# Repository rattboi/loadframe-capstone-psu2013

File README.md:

loadframe-capstone-psu2013
==========================

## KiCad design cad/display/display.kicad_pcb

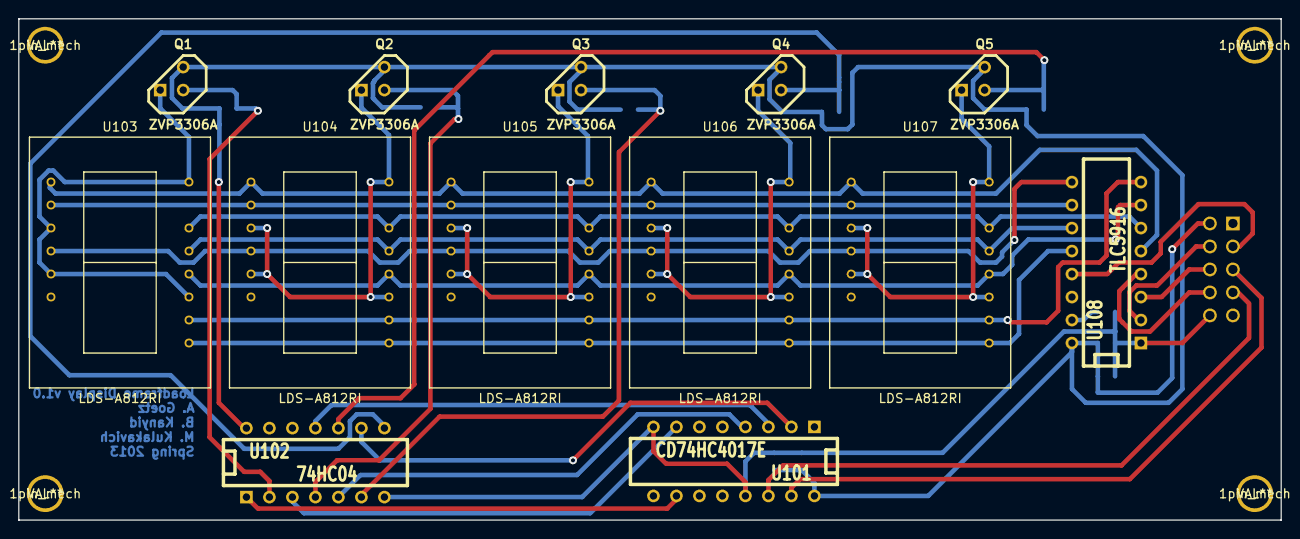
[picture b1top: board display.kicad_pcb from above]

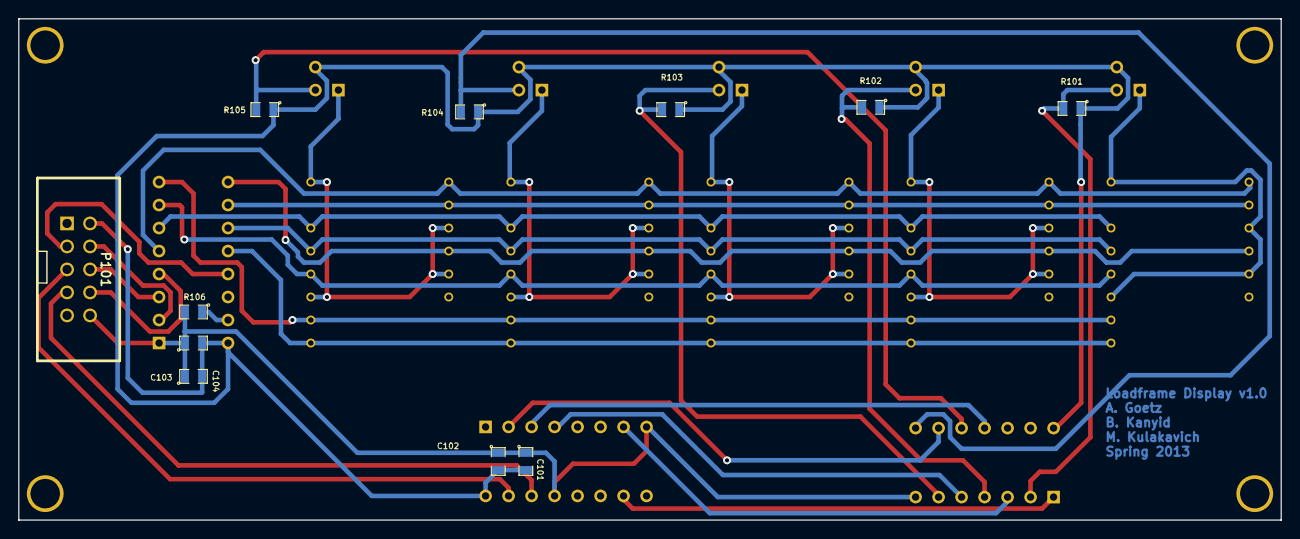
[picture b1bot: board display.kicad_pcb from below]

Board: 2 copper layers, 139.4 x 55.4 mm, 28 parts (11 on the bottom side), 32 nets.

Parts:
1pin_mech, 1pin_mech#2, 1pin_mech#3, 1pin_mech#4: VAL**; 1pin_mech
C101, C103: 100nF; SM0805
C102, C104: 1uF; SM0805
P101: CONN_5X2; shrouded_5x2
Q1, Q2, Q3, Q4, Q5: ZVP3306A; TO92-123
R101, R102, R103, R104, R105: 10K; SM0805
R106: 750; SM0805
U101: CD74HC4017E; DIP-16__300
U102: 74HC04; DIP-14__300
U103, U104, U105, U106, U107: LDS-A812RI
U108: TLC5916; DIP-16__300

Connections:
+5V: C101.2, C102.2, C103.2, C104.2, P101.2, Q1.1, Q2.1, Q3.1, Q4.1, Q5.1, R101.1, R102.1, R103.1, R104.1, R105.1, U101.16, U102.14, U108.16
/A: U103.1, U104.1, U105.1, U106.1, U107.1, U108.5
/B: U103.14, U104.14, U105.14, U106.14, U107.14, U108.6
/C: U103.12, U104.12, U105.12, U106.12, U107.12, U108.7
/D: U103.10, U104.10, U105.10, U106.10, U107.10, U108.8
/E: U103.4, U104.4, U105.4, U106.4, U107.4, U108.9
/F: U103.2, U104.2, U105.2, U106.2, U107.2, U108.10
/G: U103.13, U104.13, U105.13, U106.13, U107.13, U108.11
/RDP: U103.9, U104.9, U105.9, U106.9, U107.9, U108.12
GND: C101.1, C102.1, C103.1, C104.1, P101.10, R106.2, U101.8, U101.13, U102.7, U108.1
unnamed: Q4.3, U106.3, U106.5, U106.11, U106.16
unnamed: U101.3, U102.11
unnamed: Q1.3, U103.3, U103.5, U103.11, U103.16
unnamed: U101.10, U102.1
unnamed: R106.1, U108.15
unnamed: P101.3, U108.13
unnamed: P101.8, U108.4
unnamed: P101.6, U108.3
unnamed: P101.4, U108.2
unnamed: U101.7, U102.3
unnamed: Q5.2, R105.2, U102.10
unnamed: Q4.2, R104.2, U102.8
unnamed: Q1.2, R101.2, U102.2
unnamed: Q2.3, U104.3, U104.5, U104.11, U104.16
unnamed: Q3.2, R103.2, U102.6
unnamed: Q3.3, U105.3, U105.5, U105.11, U105.16
unnamed: U101.2, U102.9
unnamed: Q2.2, R102.2, U102.4
unnamed: Q5.3, U107.3, U107.5, U107.11, U107.16
unnamed: U101.4, U102.5
unnamed: P101.7, U101.14
unnamed: P101.5, U101.15

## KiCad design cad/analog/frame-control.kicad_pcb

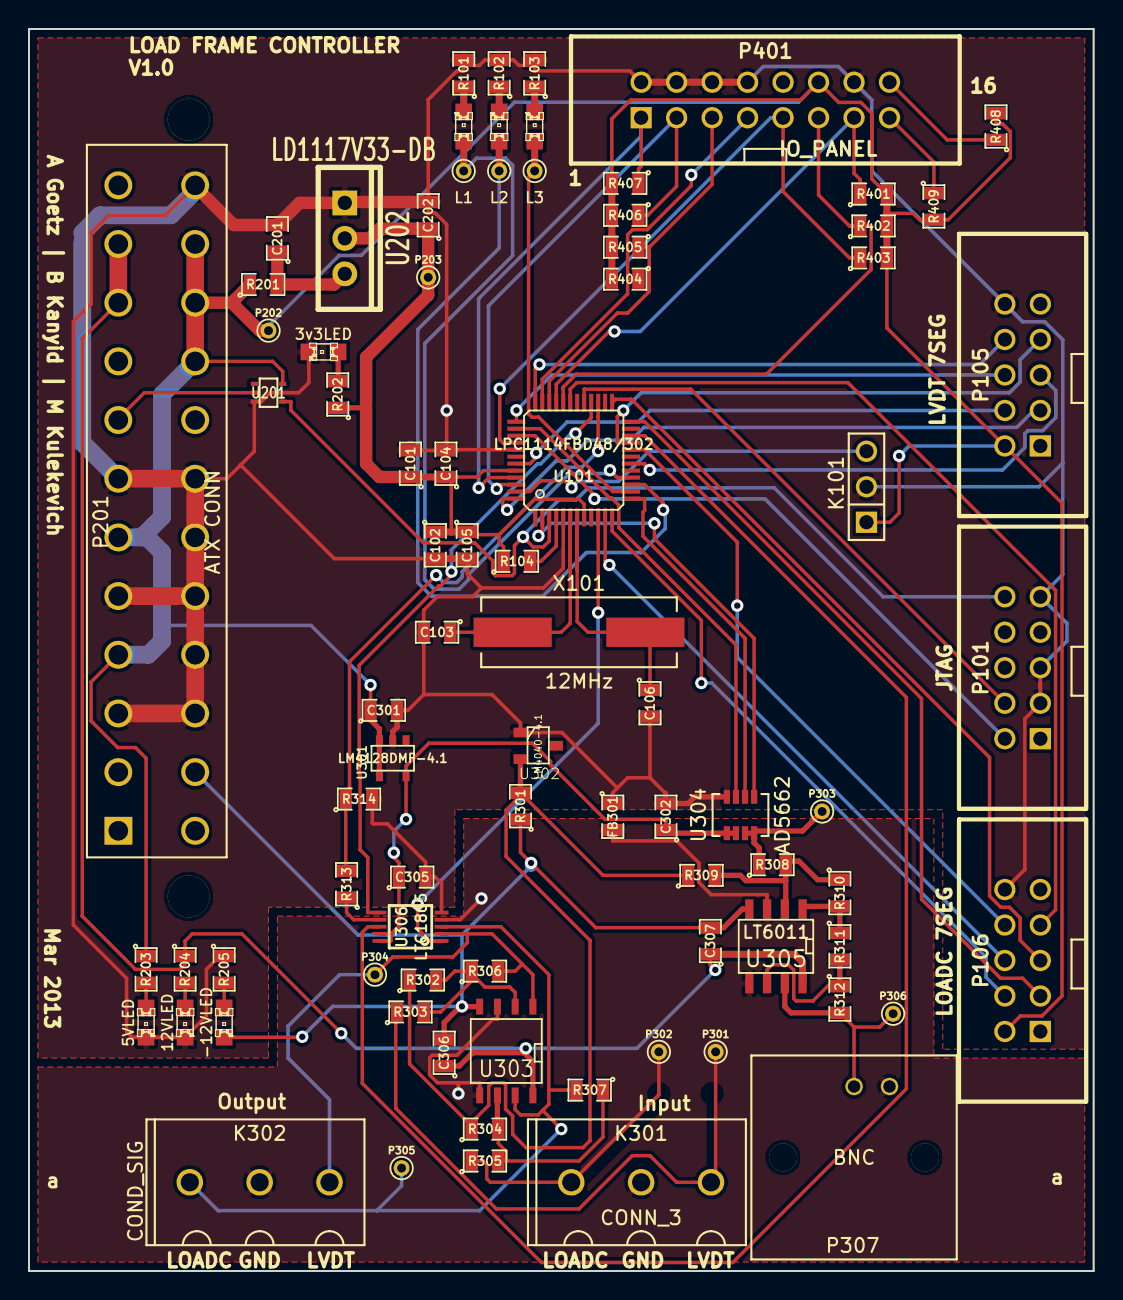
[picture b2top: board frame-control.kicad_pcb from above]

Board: 2 copper layers, 76.2 x 88.9 mm, 83 parts (0 on the bottom side), 67 nets.

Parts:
C101, C102, C302, C305, C306, C307: 100n; SM0805
C103, C106: 18pF; SM0805
C104, C105: 10n; SM0805
C201, C202: 1u; SM0805
C301: 4.7u; SM0805
D101: L1; LED-0805
D102: L2; LED-0805
D103: L3; LED-0805
D201: 3v3LED; LED-0805
D202: 5VLED; LED-0805
D203: 12VLED; LED-0805
D204: -12VLED; LED-0805
FB301: FILTER; SM0805
K101: LCD; PIN_ARRAY_3X1
K301: CONN_3; OSTTA030161
K302: COND_SIG; OSTTA030161
P101: JTAG; shrouded_5x2
P102, P103, P104, P202, P203, P301, P302, P303, P304, P305, P306: TST; PINTST
P105: LVDT; shrouded_5x2
P106: LOADC; shrouded_5x2
P201: ATX CONN; 39-29-9242
P307: BNC; TE-1-1634612-0
P401: IO_PANEL; shrouded_8x2
R101, R102, R103, R202, R203, R204, R205: 1.5k; SM0805
R104, R306, R307, R308, R310, R313, R314, R403, R404, R405, R406, R407, R408, R409: 10k; SM0805
R201: 0; SM0805
R301: 500; SM0805
R302, R304, R309: 20k; SM0805
R303, R305: 59k; SM0805
R311: 17k; SM0805
R312: 100k; SM0805
R401, R402: 5.1k; SM0805
U101: LPC1114FBD48/302; lqfp48
U201: 74LVCE1G06; SOT353
U202: LD1117V33-DB; TO220_VERT_FIX
U301: LM4128DMF-4.1; SOT23-5
U302: LM4040-4.1; SOT23
U303: LT6011; SO8N
U304: AD5662; SOT23-8
U305: LT6011; SO8E
U306: LTC1865; MSOP10-0.5
X101: 12MHz; HC-49-US

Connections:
+3.3V: C101.1, C102.1, C104.1, C105.1, C202.1, P203.1, R104.1, R202.1, U101.8, U101.44, U202.2
+5V: C301.1, K101.1, P105.2, P106.2, P201.4, P201.6, P201.21, P201.22, P201.23, P202.1, P401.12, R201.1, R203.1, R401.2, R402.2, R403.2, R404.2, R405.2, R406.2, R407.2, R408.2, R409.2, U201.5, U301.3, U301.4
+5VA: C302.1, C305.1, U301.5, U304.1, U304.2, U306.9, U306.10
+12V: C306.1, C307.1, P201.10, P201.11, R204.1, U303.8, U305.8
-12V: C306.2, C307.2, D204.2, P201.14, R301.1, U303.4, U305.4
/Analog Frontend/ADCCLK: U101.22, U306.8
/Analog Frontend/ADCEN: U101.10, U306.1
/Analog Frontend/ADCI: U101.28, U306.6
/Analog Frontend/ADCO: R313.2, R314.1, U101.27
/Analog Frontend/DACCLK: U101.13, U304.6
/Analog Frontend/DACIN: U101.38, U304.7
/Analog Frontend/~DACEN: U101.2, U304.5
/InterfaceButtons/Aux1: P401.15, R409.1
/InterfaceButtons/Aux2: P401.16, R408.1
/InterfaceButtons/ESTOP: P401.5, R405.1, U101.34
/InterfaceButtons/EncoderA: P401.11, R402.1, U101.32
/InterfaceButtons/EncoderB: P401.13, R401.1, U101.33
/InterfaceButtons/TareLOADC: P401.3, R406.1, U101.46
/InterfaceButtons/TareLVDT: P401.1, R407.1, U101.45
/InterfaceButtons/ToggleA: P401.7, R404.1, U101.35
/InterfaceButtons/ToggleB: P401.9, R403.1, U101.40
/Power/PWRGD: P101.10, U101.3, U201.4
AGND: FB301.2, K301.2, K302.2, P307.2, U303.3, U303.5, U305.3, U305.5, U306.4
GND: C101.2, C102.2, C103.2, C104.2, C105.2, C106.2, C201.2, C202.2, C301.2, C302.2, C305.2, D201.2, D202.2, D203.2, FB301.1, K101.2, P101.3, P101.5, P101.9, P105.10, P106.10, P201.3, P201.5, P201.7, P201.15, P201.16, P201.17, P201.18, P201.19, P201.24, P401.2, P401.4, P401.6, P401.8, P401.14, R101.2, R102.2, R103.2, R205.1, R314.2, U101.5, U101.41, U201.3, U202.1, U301.2, U302.1, U304.8, U306.5
unnamed: P106.6, U101.11
unnamed: P106.8, U101.20
unnamed: C103.1, U101.6, X101.1
unnamed: C106.1, U101.7, X101.2
unnamed: P105.6, U101.37
unnamed: P105.8, U101.36
unnamed: P106.5, U101.25
unnamed: P105.5, U101.18
unnamed: P105.3, U101.48
unnamed: P105.4, U101.43
unnamed: P106.7, U101.31
unnamed: P106.3, U101.24
unnamed: P106.4, U101.12
unnamed: R104.2, U101.4
unnamed: P105.7, U101.21
unnamed: K101.3, U101.47
unnamed: P101.4, U101.29
unnamed: P101.2, U101.39
unnamed: D102.1, P103.1, U101.15
unnamed: D102.2, R102.1
unnamed: D101.1, P102.1, U101.16
unnamed: D101.2, R101.1
unnamed: D103.1, P104.1, U101.14
unnamed: D103.2, R103.1
unnamed: R313.1, U306.7
unnamed: R302.2, R303.2, R306.1, U303.2
unnamed: K302.3, P304.1, R306.2, U303.1, U306.2
unnamed: K301.3, P301.1, R303.1
unnamed: R301.2, R302.1, R304.1, R309.1, U302.2
unnamed: K301.1, P302.1, R305.1
unnamed: P303.1, R308.1, U304.3, U304.4
unnamed: R308.2, R309.2, R310.1, U305.2
unnamed: K302.1, P305.1, R307.2, U303.7, U306.3
unnamed: P306.1, P307.1, R312.2, U305.7
unnamed: R304.2, R305.2, R307.1, U303.6
unnamed: R310.2, R311.1, U305.1
unnamed: R311.2, R312.1, U305.6
unnamed: D201.1, R202.2
unnamed: D202.1, R203.2
unnamed: D204.1, R205.2
unnamed: D203.1, R204.2
unnamed: C201.1, R201.2, U202.3
unnamed: P201.8, U201.2

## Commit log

2013-01-22 Added skeleton of requirements document
2013-01-23 Added basic requirements.
2013-02-27 Added LTSpice simulations of OPAMP circuits
2013-02-27 Changed references in opamp circuits to be -5.0 volts
2013-02-27 started work on kicad schematic
2013-03-01 Wired up ADC and DAC
2013-03-01 updated models with 4.096 reference
2013-03-06 Moved Andy's analog frontend into it's own directory
2013-03-06 Added .gitignore for annoying Kicad backups Added root to display board
2013-03-06 Added $blah.brd to .gitignore because they're annoying
2013-03-08 First version of display schematic
2013-03-22 added support logic to analog drawing
2013-03-25 Finished first version of schematic
2013-03-26 started work on analog pcb
2013-03-28 added a lot more to the pcb design
2013-03-28 fixed issue with weird rendered blobs in gerbers
2013-03-29 added psu logo and adjust some traces
2013-04-05 modified schematic to add stapling
2013-04-10 Updated schematic layout
2013-04-10 Added moar ferrite beads and widened power traces
2013-04-11 Changed a power trace width
2013-04-12 1st pass on display layout. Footprints need work
2013-04-13 Rev2 of displayboard,needs borders + holes
2013-04-13 Added bom files
2013-04-13 Modified values to be values that can be found on digikey
2013-04-13 Added readme to bom directory
2013-04-13 Committing the real v2 display layout
2013-04-13 Added csv of frame-control bom
2013-04-13 Updated DAC simulation to reflect new part value
2013-04-14 Ground fills added, mounting holes too
    Text also added. I think this is done.
2013-04-14 Created BOM for display board
2013-04-14 Filter more files in .gitignore
2013-04-14 Rev2 of board w/ right transistors (PMOS SUCKS)
2013-04-14 Modified loadframe pcb to have additionaly auxiliary button
2013-04-18 PCB update (remove groundplane for EPL print)
2013-04-23 added lpc code
2013-04-27 Added code to drive first gpio
2013-04-27 Worked on dac driver. Think it works naow
2013-04-28 Dac code works naow
2013-04-29 Added support for adc
2013-04-30 Added support for 7seg (rudimentary right now)
2013-04-30 Added function to write out number to lcd
2013-05-10 Changed trace width to 20 mils. Had to move some things around
2013-05-10 Both screens are working
2013-05-22 Blinking works, some buttons work, both screens work
2013-05-25 Got toggle and encoder functions, verified the I/O
    need to work on the logic
2013-05-25 It shows stuffs like setpoints, per digits
2013-05-25 added negative
2013-05-27 added emacs backup files to gitignore
2013-05-27 Updated PCBs with latest changes
2013-05-27 Numbers works better, refactored some encoder stuff
2013-05-29 conv_to_voltage for DAC is working, with some samples
2013-05-29 Added most of the mode logic. It's broke right now though
2013-05-30 Everything is working, except loadcell and some feedback issues
    Setpoint stuff needs to be better
2013-05-30 added poster
2013-05-31 Removed a lot of magic constants, fakey proportional execute
    modified gitignore to ignore Debug stuff
    removed Debug files that were being tracked
    Code refactor of some UI stuff
    DEFINES for IO stuff
2013-05-31 updated manual
2013-05-31 added tld
2013-05-31 Refactored everything, house cleaning
    Moved mod_setpoint into main.c
    A lot of tab/spacing cleanup
    Added "-set-" to Loadcell disp when in setpoint mode
    Removed all the magic constants, pretty much.
    - Everything should be configurable through #defines and consts.
2013-06-01 Made code not executable (-x)
2013-06-01 worked on manual
2013-06-01 Added stub for loadcell scaling, also fixed math for conversions
2013-06-01 Minor editing and corrections to manual
2013-06-02 Fixed voltage directions in manual
2013-06-02 Poster is further along, but not far enough.
2013-06-02 Put some captions on some images
2013-06-02 made it better
2013-06-02 even moar bitchin
2013-06-02 First pass edit
2013-06-13 Added support for speed control (preliminary)
    Timer added for specific control of speed
    A bunch of other stuff
2013-06-13 Speed Control is working
